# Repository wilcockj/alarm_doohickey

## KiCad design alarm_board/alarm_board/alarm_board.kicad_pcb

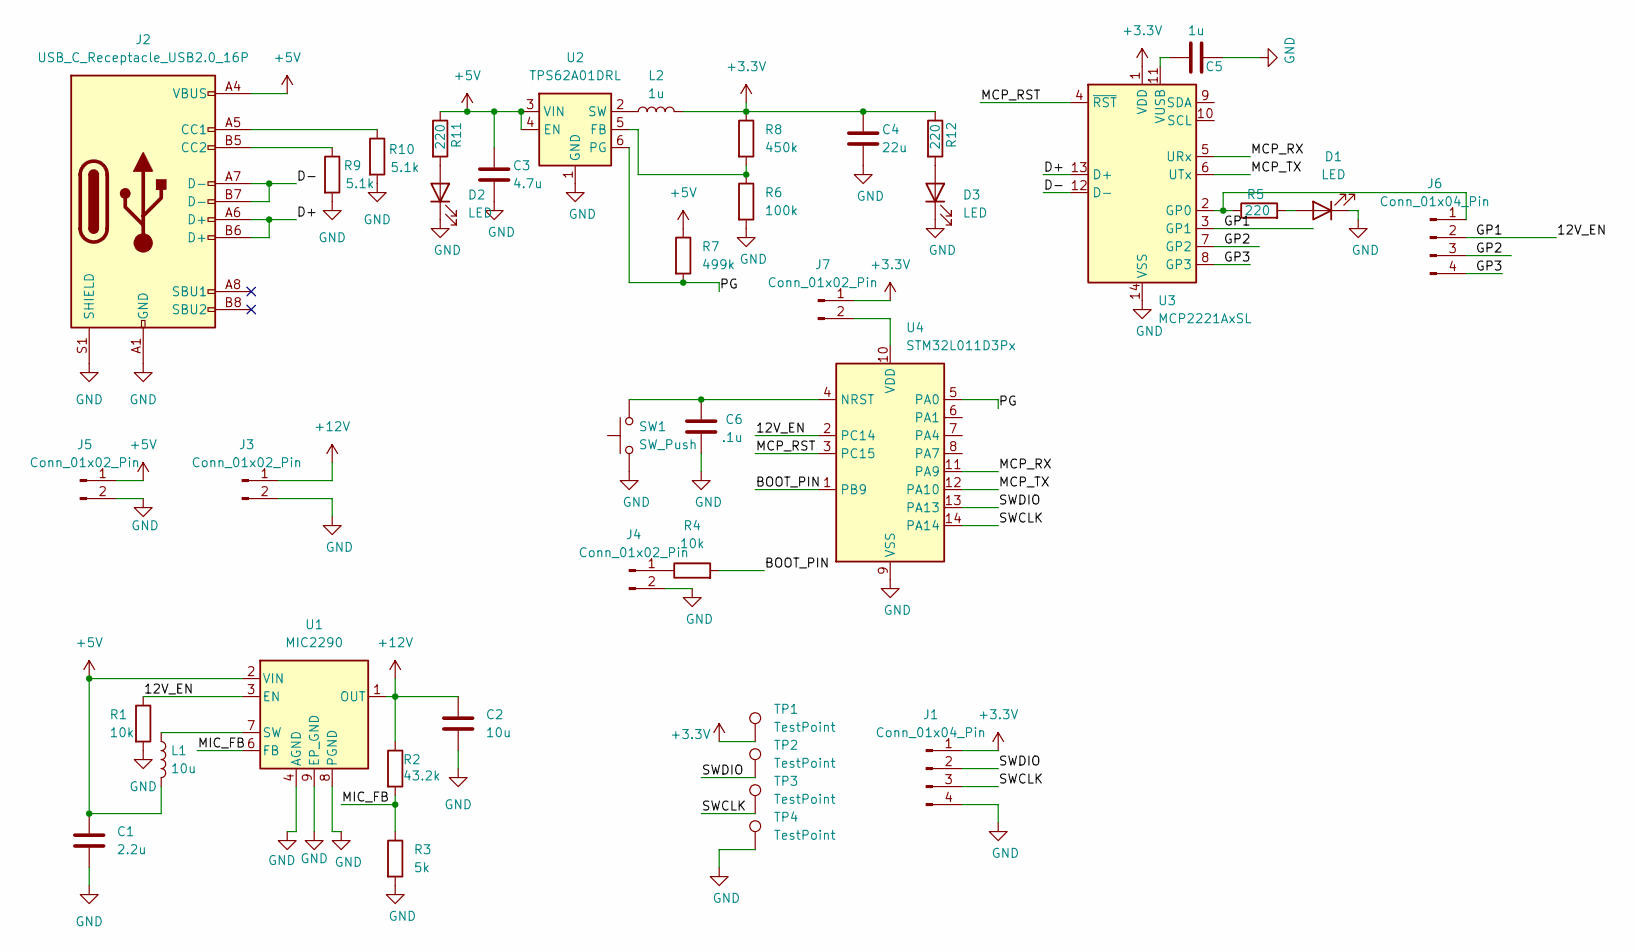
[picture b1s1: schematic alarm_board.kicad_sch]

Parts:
C1: 2.2u; C_1206_3216Metric
C2: 10u; C_1206_3216Metric
C3: 4.7u; C_1206_3216Metric
C4: 22u; C_1206_3216Metric
C5: 1u; C_1206_3216Metric
C6: .1u; C_1206_3216Metric
D1, D2, D3: LED; LED_1206_3216Metric
J1, J6: Conn_01x04_Pin; PinHeader_1x04_P2.54mm_Vertical
J2: USB_C_Receptacle_USB2.0_16P; USB_C_Receptacle_HCTL_HC-TYPE-C-16P-01A
J3: Conn_01x02_Pin; JST_XH_S2B-XH-A_1x02_P2.50mm_Horizontal
J4, J5, J7: Conn_01x02_Pin; PinHeader_1x02_P2.54mm_Vertical
L1: 10u; L_1206_3216Metric
L2: 1u; L_1206_3216Metric
R1, R4: 10k; R_1206_3216Metric
R2: 43.2k; R_1206_3216Metric
R3: 5k; R_1206_3216Metric
R5, R11, R12: 220; R_1206_3216Metric
R6: 100k; R_1206_3216Metric
R7: 499k; R_1206_3216Metric
R8: 450k; R_1206_3216Metric
R9, R10: 5.1k; R_1206_3216Metric
SW1: SW_Push; SW_Push_1P1T_NO_CK_KMR2
TP1, TP2, TP3, TP4: TestPoint; TestPoint_Pad_D2.0mm
U1: MIC2290; Micrel_MLF-8-1EP_2x2mm_P0.5mm_EP0.8x1.3mm_ThermalVias
U2: TPS62A01DRL; SOT-563
U3: MCP2221AxSL; SOIC-14_3.9x8.7mm_P1.27mm
U4: STM32L011D3Px; TSSOP-14_4.4x5mm_P0.65mm

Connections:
+3.3V: C4.1, J1.1, J7.1, L2.2, R8.1, R12.1, TP1.1, U3.1 (VDD)
+5V: C1.1, C3.1, J2.A4 (VBUS), J2.A9 (VBUS), J2.B4 (VBUS), J2.B9 (VBUS), J5.1, L1.2, R7.1, R11.1, U1.2 (VIN), U2.3 (VIN), U2.4 (EN)
+12V: C2.1, J3.1, R2.1, U1.1 (OUT)
/12V_EN: J6.2, R1.1, U1.3 (EN), U3.3 (GP1), U4.2 (PC14)
/BOOT_PIN: R4.2, U4.1 (PB9)
/D+: J2.A6 (D+), J2.B6 (D+), U3.13 (D+)
/D-: J2.A7 (D-), J2.B7 (D-), U3.12 (D-)
/GP2: J6.3, U3.7 (GP2)
/GP3: J6.4, U3.8 (GP3)
/MCP_RST: U3.4 (~RST), U4.3 (PC15)
/MCP_RX: U3.5 (URx), U4.11 (PA9)
/MCP_TX: U3.6 (UTx), U4.12 (PA10)
/MIC_FB: R2.2, R3.1, U1.6 (FB)
/PG: R7.2, U2.6 (PG), U4.5 (PA0)
/SWCLK: J1.3, TP3.1, U4.14 (PA14)
/SWDIO: J1.2, TP2.1, U4.13 (PA13)
GND: C1.2, C2.2, C3.2, C4.2, C5.2, C6.2, D1.1 (K), D2.1 (K), D3.1 (K), J1.4, J2.A1 (GND), J2.A12 (GND), J2.B1 (GND), J2.B12 (GND), J2.S1 (SHIELD), J3.2, J4.2, J5.2, R1.2, R3.2, R6.2, R9.2, R10.2, SW1.1, TP4.1, U1.4 (AGND), U1.8 (PGND), U1.9 (EP_GND), U2.1 (GND), U3.14 (VSS), U4.9 (VSS)
unnamed: D1.2 (A), R5.2
unnamed: D2.2 (A), R11.2
unnamed: D3.2 (A), R12.2
unnamed: J2.A5 (CC1), R10.1
unnamed: J2.B5 (CC2), R9.1
unnamed: J4.1, R4.1
unnamed: J6.1, R5.1, U3.2 (GP0)
unnamed: J7.2, U4.10 (VDD)
unnamed: L1.1, U1.7 (SW)
unnamed: R6.1, R8.2, U2.5 (FB)
unnamed: L2.1, U2.2 (SW)
unnamed: C5.1, U3.11 (VUSB)
unnamed: C6.1, SW1.2, U4.4 (NRST)

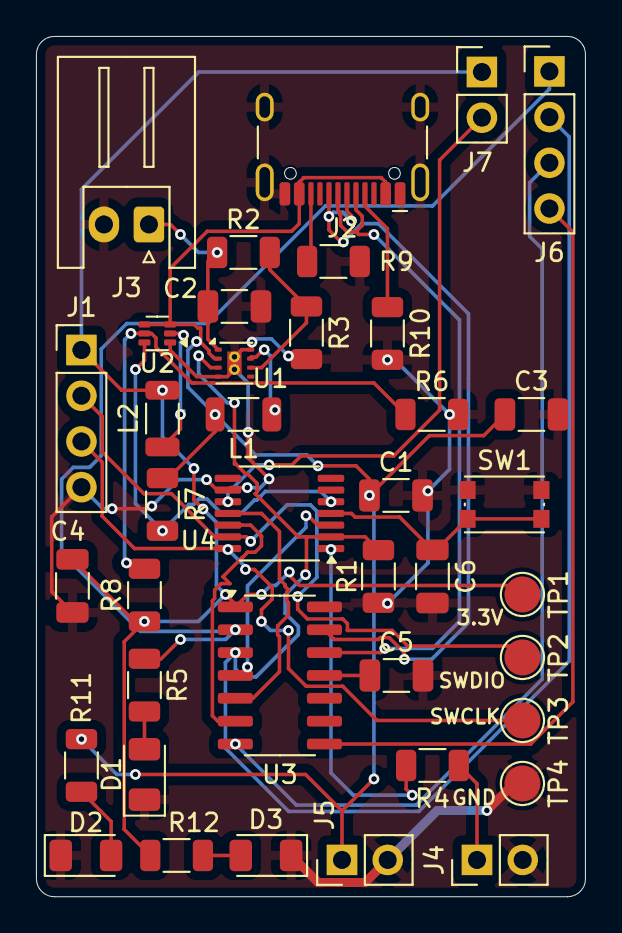
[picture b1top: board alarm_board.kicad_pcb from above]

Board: 2 copper layers, 30.5 x 47.8 mm, 39 parts (0 on the bottom side), 30 nets.

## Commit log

2025-06-06 initial commit for doohickey
2025-06-07 added headers for 5v and boot
2025-06-07 first pass of routing
2025-06-07 updated proj file
2025-06-07 got board a little smaller
2025-06-09 added header jumper for stm32 powering optional
